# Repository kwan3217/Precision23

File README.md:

# Precision23
Project Precision updated to 2023

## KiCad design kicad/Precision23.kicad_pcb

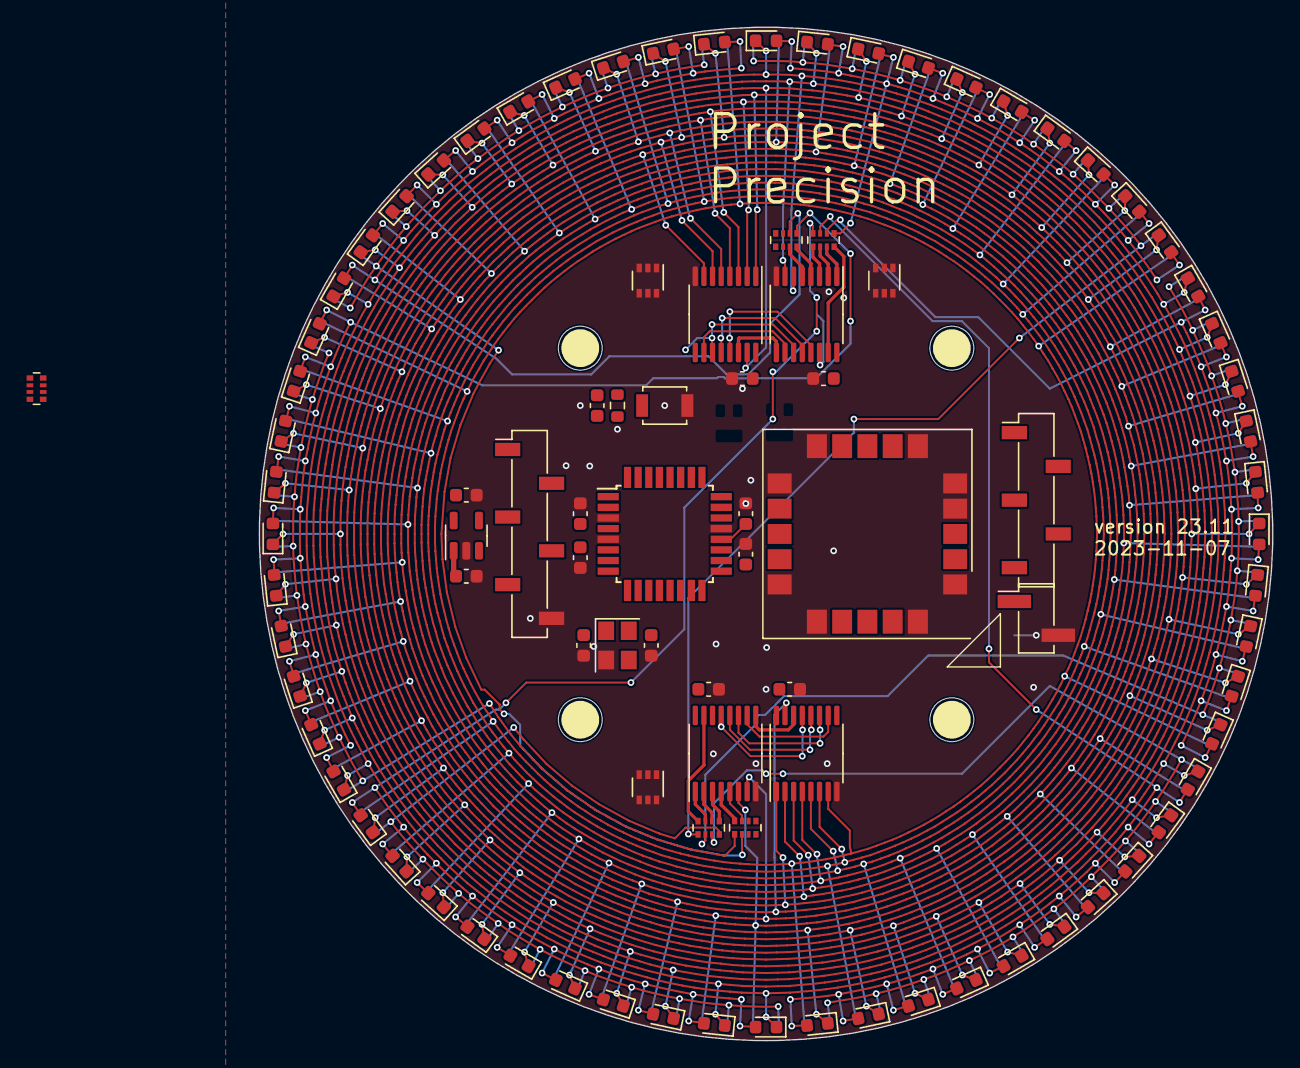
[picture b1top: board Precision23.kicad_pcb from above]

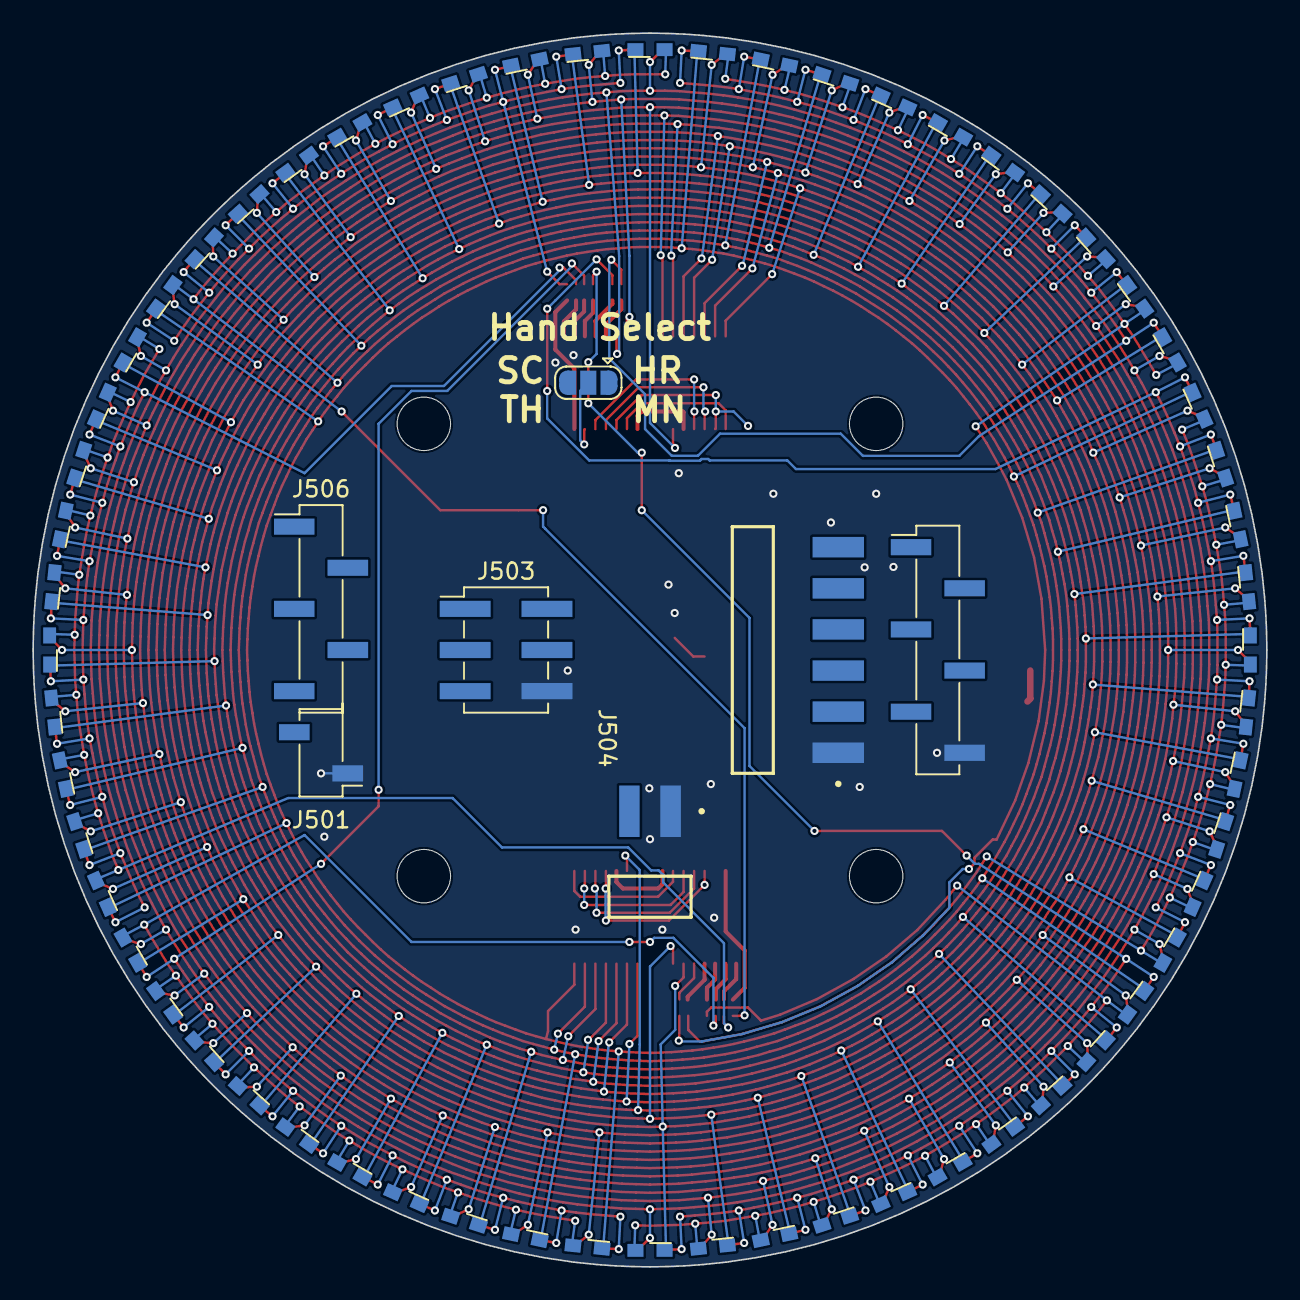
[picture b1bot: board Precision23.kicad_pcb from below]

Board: 2 copper layers, 76.2 x 76.2 mm, 166 parts (67 on the bottom side), 75 nets.

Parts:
C001, C002, C101, C102, C404, C406, C418, C420, C506: 100nF; C_0603_1608Metric
C407, C408: 22pF; C_0603_1608Metric
C601, C605: 1uF; C_0603_1608Metric
D000, D001, D002, D003, D004, D005, D006, D007, D008, D009, D010, D011, D012, D013, D014, D015, D016, D017, D018, D019, D020, D021, D022, D023, D024, D025, D026, D027, D028, D029, D030, D031, D032, D033, D034, D035, D036, D037, D038, D039, D040, D041, D042, D043, D044, D045, D046, D047, D048, D049, D050, D051, D052, D053, D054, D055, D056, D057, D058, D059: B; LED_0603_1608Metric
D100, D101, D102, D103, D104, D105, D106, D107, D108, D109, D110, D111, D112, D113, D114, D115, D116, D117, D118, D119, D120, D121, D122, D123, D124, D125, D126, D127, D128, D129, D130, D131, D132, D133, D134, D135, D136, D137, D138, D139, D140, D141, D142, D143, D144, D145, D146, D147, D148, D149, D150, D151, D152, D153, D154, D155, D156, D157, D158, D159: G; D_KINGBRIGHT_DOME
G101: KwanSystems; PrecisionKwan
J501: Conn_01x02_Pin; PinSocket_1x02_P2.54mm_Vertical_SMD_Pin1Left
J502: Conn_01x02_Pin; PinHeader_1x02_P2.54mm_Vertical_SMD_Pin1Left
J503: Conn_02x03_Odd_Even; PinHeader_2x03_P2.54mm_Vertical_SMD
J504: Conn_01x06; SAMTEC_TSM-106-01-T-SH
J505: Conn_01x06; PinHeader_1x06_P2.54mm_Vertical_SMD_Pin1Left
J506: Conn_01x05; PinHeader_1x05_P2.54mm_Vertical_SMD_Pin1Left
J507: Conn_01x05; PinSocket_1x05_P2.54mm_Vertical_SMD_Pin1Left
J508: Conn_01x06; PinSocket_1x06_P2.54mm_Vertical_SMD_Pin1Left
J509: Conn_01x02_Pin; SAMTEC_TSM-102-01-T-SH
J596, J597, J598, J599: STANDOFF; STANDOFF_NONPLATED
R001, R002, R101, R102: RP4; R_Array_Convex_4x0402
R429: 10k; R_0603_1608Metric
R506: 10k; R_Array_Convex_4x0402
S429: SW_SPST; SW_SPST_B3U-1000P
S501: SolderJumper_3_Open; SolderJumper-3_P1.3mm_Open_RoundedPad1.0x1.5mm
U001, U002, U101, U102: 74HC595; TSSOP-16_4.4x5mm_P0.65mm
U401: ATMEGA328P-AU; TQFP-32_7x7mm_P0.8mm
U501: SAM-M8Q; ublox_SAM-M8Q
U502, U503, U504: NC7SZ157; SOT-363_SC-70-6
U601: TCR2EF 3.3V; SOT-23-5
Y407: 16MHz; Crystal_SMD_3225-4Pin_3.2x2.5mm

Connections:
+3V3: C001.1, C002.1, C101.1, C102.1, C404.1, C406.1, C418.1, C605.1, J503.2, J504.3, J505.4, J508.4, R429.1, R506.6 (5), R506.7 (5), R506.8 (5), U001.16 (VCC), U002.16 (VCC), U101.16 (VCC), U102.16 (VCC), U401.4 (VCC), U401.6 (VCC), U401.18 (AVCC), U501.2 (VCC_IO), U501.3 (V_BCKP), U501.17 (VCC), U502.5 (VCC), U503.5 (VCC), U504.5 (VCC), U601.5 (OUT)
/AT_RX: U401.30 (PD0), U502.4 (OUT)
/AT_TX: U401.31 (PD1), U503.3 (I0), U504.1 (I1)
/DTR: C506.2, J504.6, J505.1, J508.1
/GPS_RX: U501.14 (RXD), U503.4 (OUT)
/GPS_TX: U501.13 (TXD), U502.3 (I0), U504.3 (I0)
/Hour hand/CASCADE: U001.9 (QH'), U002.14 (SER)
/Hour hand/H0x: D000.2 (A), D001.2 (A), D002.2 (A), D003.2 (A), D004.2 (A), D005.2 (A), D006.2 (A), D007.2 (A), D008.2 (A), D009.2 (A), R001.5
/Hour hand/H1x: D010.2 (A), D011.2 (A), D012.2 (A), D013.2 (A), D014.2 (A), D015.2 (A), D016.2 (A), D017.2 (A), D018.2 (A), D019.2 (A), R001.6 (5)
/Hour hand/H2x: D020.2 (A), D021.2 (A), D022.2 (A), D023.2 (A), D024.2 (A), D025.2 (A), D026.2 (A), D027.2 (A), D028.2 (A), D029.2 (A), R001.7 (5)
/Hour hand/H3x: D030.2 (A), D031.2 (A), D032.2 (A), D033.2 (A), D034.2 (A), D035.2 (A), D036.2 (A), D037.2 (A), D038.2 (A), D039.2 (A), R001.8 (5)
/Hour hand/H4x: D040.2 (A), D041.2 (A), D042.2 (A), D043.2 (A), D044.2 (A), D045.2 (A), D046.2 (A), D047.2 (A), D048.2 (A), D049.2 (A), R002.5
/Hour hand/H5x: D050.2 (A), D051.2 (A), D052.2 (A), D053.2 (A), D054.2 (A), D055.2 (A), D056.2 (A), D057.2 (A), D058.2 (A), D059.2 (A), R002.6 (5)
/Hour hand/Hx0: D000.1 (K), D010.1 (K), D020.1 (K), D030.1 (K), D040.1 (K), D050.1 (K), U001.6 (QG)
/Hour hand/Hx1: D001.1 (K), D011.1 (K), D021.1 (K), D031.1 (K), D041.1 (K), D051.1 (K), U001.7 (QH)
/Hour hand/Hx2: D002.1 (K), D012.1 (K), D022.1 (K), D032.1 (K), D042.1 (K), D052.1 (K), U002.15 (QA)
/Hour hand/Hx3: D003.1 (K), D013.1 (K), D023.1 (K), D033.1 (K), D043.1 (K), D053.1 (K), U002.1 (QB)
/Hour hand/Hx4: D004.1 (K), D014.1 (K), D024.1 (K), D034.1 (K), D044.1 (K), D054.1 (K), U002.2 (QC)
/Hour hand/Hx5: D005.1 (K), D015.1 (K), D025.1 (K), D035.1 (K), D045.1 (K), D055.1 (K), U002.3 (QD)
/Hour hand/Hx6: D006.1 (K), D016.1 (K), D026.1 (K), D036.1 (K), D046.1 (K), D056.1 (K), U002.4 (QE)
/Hour hand/Hx7: D007.1 (K), D017.1 (K), D027.1 (K), D037.1 (K), D047.1 (K), D057.1 (K), U002.5 (QF)
/Hour hand/Hx8: D008.1 (K), D018.1 (K), D028.1 (K), D038.1 (K), D048.1 (K), D058.1 (K), U002.6 (QG)
/Hour hand/Hx9: D009.1 (K), D019.1 (K), D029.1 (K), D039.1 (K), D049.1 (K), D059.1 (K), U002.7 (QH)
/Hour hand/P0x: R001.4, U001.15 (QA)
/Hour hand/P1x: R001.3 (4), U001.1 (QB)
/Hour hand/P2x: R001.2 (4), U001.2 (QC)
/Hour hand/P3x: R001.1 (4), U001.3 (QD)
/Hour hand/P4x: R002.4, U001.4 (QE)
/Hour hand/P5x: R002.3 (4), U001.5 (QF)
/Minute hand/CASCADE: U101.9 (QH'), U102.14 (SER)
/Minute hand/M0x: D100.2 (A), D101.2 (A), D102.2 (A), D103.2 (A), D104.2 (A), D105.2 (A), D106.2 (A), D107.2 (A), D108.2 (A), D109.2 (A), R101.5
/Minute hand/M1x: D110.2 (A), D111.2 (A), D112.2 (A), D113.2 (A), D114.2 (A), D115.2 (A), D116.2 (A), D117.2 (A), D118.2 (A), D119.2 (A), R101.6 (5)
/Minute hand/M2x: D120.2 (A), D121.2 (A), D122.2 (A), D123.2 (A), D124.2 (A), D125.2 (A), D126.2 (A), D127.2 (A), D128.2 (A), D129.2 (A), R101.7 (5)
/Minute hand/M3x: D130.2 (A), D131.2 (A), D132.2 (A), D133.2 (A), D134.2 (A), D135.2 (A), D136.2 (A), D137.2 (A), D138.2 (A), D139.2 (A), R101.8 (5)
/Minute hand/M4x: D140.2 (A), D141.2 (A), D142.2 (A), D143.2 (A), D144.2 (A), D145.2 (A), D146.2 (A), D147.2 (A), D148.2 (A), D149.2 (A), R102.5
/Minute hand/M5x: D150.2 (A), D151.2 (A), D152.2 (A), D153.2 (A), D154.2 (A), D155.2 (A), D156.2 (A), D157.2 (A), D158.2 (A), D159.2 (A), R102.6 (5)
/Minute hand/Mx0: D100.1 (K), D110.1 (K), D120.1 (K), D130.1 (K), D140.1 (K), D150.1 (K), U101.6 (QG)
/Minute hand/Mx1: D101.1 (K), D111.1 (K), D121.1 (K), D131.1 (K), D141.1 (K), D151.1 (K), U101.7 (QH)
/Minute hand/Mx2: D102.1 (K), D112.1 (K), D122.1 (K), D132.1 (K), D142.1 (K), D152.1 (K), U102.15 (QA)
/Minute hand/Mx3: D103.1 (K), D113.1 (K), D123.1 (K), D133.1 (K), D143.1 (K), D153.1 (K), U102.1 (QB)
/Minute hand/Mx4: D104.1 (K), D114.1 (K), D124.1 (K), D134.1 (K), D144.1 (K), D154.1 (K), U102.2 (QC)
/Minute hand/Mx5: D105.1 (K), D115.1 (K), D125.1 (K), D135.1 (K), D145.1 (K), D155.1 (K), U102.3 (QD)
/Minute hand/Mx6: D106.1 (K), D116.1 (K), D126.1 (K), D136.1 (K), D146.1 (K), D156.1 (K), U102.4 (QE)
/Minute hand/Mx7: D107.1 (K), D117.1 (K), D127.1 (K), D137.1 (K), D147.1 (K), D157.1 (K), U102.5 (QF)
/Minute hand/Mx8: D108.1 (K), D118.1 (K), D128.1 (K), D138.1 (K), D148.1 (K), D158.1 (K), U102.6 (QG)
/Minute hand/Mx9: D109.1 (K), D119.1 (K), D129.1 (K), D139.1 (K), D149.1 (K), D159.1 (K), U102.7 (QH)
/Minute hand/P0x: R101.4, U101.15 (QA)
/Minute hand/P1x: R101.3 (4), U101.1 (QB)
/Minute hand/P2x: R101.2 (4), U101.2 (QC)
/Minute hand/P3x: R101.1 (4), U101.3 (QD)
/Minute hand/P4x: R102.4, U101.4 (QE)
/Minute hand/P5x: R102.3 (4), U101.5 (QF)
/Nano/AREF: C420.1, U401.20 (AREF)
/Nano/D2: S501.1 (A), U401.32 (PD2)
/Nano/D3: J506.2, J507.2, U001.11 (SRCLK), U002.11 (SRCLK), U101.11 (SRCLK), U102.11 (SRCLK), U401.1 (PD3)
/Nano/D4: J506.3, J507.3, U001.10 (~SRCLR), U002.10 (~SRCLR), U101.10 (~SRCLR), U102.10 (~SRCLR), U401.2 (PD4)
/Nano/D5: J506.4, J507.4, U001.12 (RCLK), U002.12 (RCLK), U101.12 (RCLK), U102.12 (RCLK), U401.9 (PD5)
/Nano/D6: J506.5, J507.5, U001.13 (~OE), U002.13 (~OE), U101.13 (~OE), U102.13 (~OE), U401.10 (PD6)
/Nano/D7: R506.1 (4), U401.11 (PD7), U502.6 (SEL)
/Nano/D8: R506.2 (4), U401.12 (PB0), U503.6 (SEL)
/Nano/D9: R506.3 (4), U401.13 (PB1), U504.6 (SEL)
/Nano/D10: U401.14 (PB2), U501.7 (TIMEPULSE)
/Nano/D11: J503.4, U401.15 (PB3)
/Nano/D12: J503.1, U401.16 (PB4)
/Nano/D13: J503.3, U401.17 (PB5)
/Nano/XTAL1: C407.2, U401.7 (XTAL1/PB6), Y407.1
/Nano/XTAL2: C408.2, U401.8 (XTAL2/PB7), Y407.3
/SER_HR_MN: U002.9 (QH'), U101.14 (SER)
/SER_IN: S501.2 (C), U001.14 (SER)
/SER_MN_SC: J506.1, J507.1, S501.3 (B), U102.9 (QH')
/USB_RX: J504.5, J505.2, J508.2, U504.4 (OUT)
/USB_TX: J504.4, J505.3, J508.3, U502.1 (I1), U503.1 (I1)
/~RESET: C506.1, J503.5, R429.2, S429.1 (A), U401.29 (~RESET/PC6)
GND: C001.2, C002.2, C101.2, C102.2, C404.2, C406.2, C407.1, C408.1, C418.2, C420.2, C601.2, C605.2, J501.1, J502.2, J503.6, J504.1, J505.6, J508.6, J509.1, S429.2 (B), U001.8 (GND), U002.8 (GND), U101.8 (GND), U102.8 (GND), U401.3 (GND), U401.5 (GND), U401.21 (GND), U501.1 (GND), U501.4 (GND), U501.5 (GND), U501.6 (GND), U501.10 (GND), U501.11 (GND), U501.15 (GND), U501.16 (GND), U501.20 (GND), U502.2 (GND), U503.2 (GND), U504.2 (GND), U601.2 (GND), Y407.2
VBUS: C601.1, J501.2, J502.1, J509.2, U601.1 (IN), U601.3 (EN)

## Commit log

2023-07-16 Added MatrixTraces, copied from old CharlieplexTraces and updated to KiCad 7.
2023-07-16 Added hands as separate sheets
2023-07-16 Added .gitignore which ignores backups
2023-07-16 Use the separate hand sheets
2023-07-16 Included updated kwan_kicad_lib
2023-07-16 Updated submodule
2023-07-17 Removed sheets that aren't used in Charlieplex
2023-07-17 Removed charlieplex sheet that isn't used in Matrix
2023-11-05 Lots of stuff
2023-11-12 Updated kwan_kicad_lib
2023-11-12 Updated to 3 multiplexers
2023-11-12 Started on LPC21xx version
2023-11-14 First completely routed version
2023-11-14 Switched PPS to D2 (has external interrupt) and therefore serial data to D10
2023-11-21 Add notes for diode voltages
2023-11-21 Add code from StackExchange to calculate diode Spice model parameters from measured diode curve.
2023-11-21 Reorganize and finish routing. This will work for 3V3 but might not be as bright as possible.
2023-11-21 Added top and bottom schematics to support refactor of board
2023-11-21 Updated .gitignore
2023-11-21 Updated references
2023-11-23 Refactored board, put 5V0 on all parts except GPS
2023-11-25 Put MOSFET switch transistors in place. We won't end up using these.
2023-11-25 Add Nano castellated slot and SMT pin header socket.
2023-11-25 Continue wiring MOSFET switches
2023-12-15 Matrix8x8 stuff
